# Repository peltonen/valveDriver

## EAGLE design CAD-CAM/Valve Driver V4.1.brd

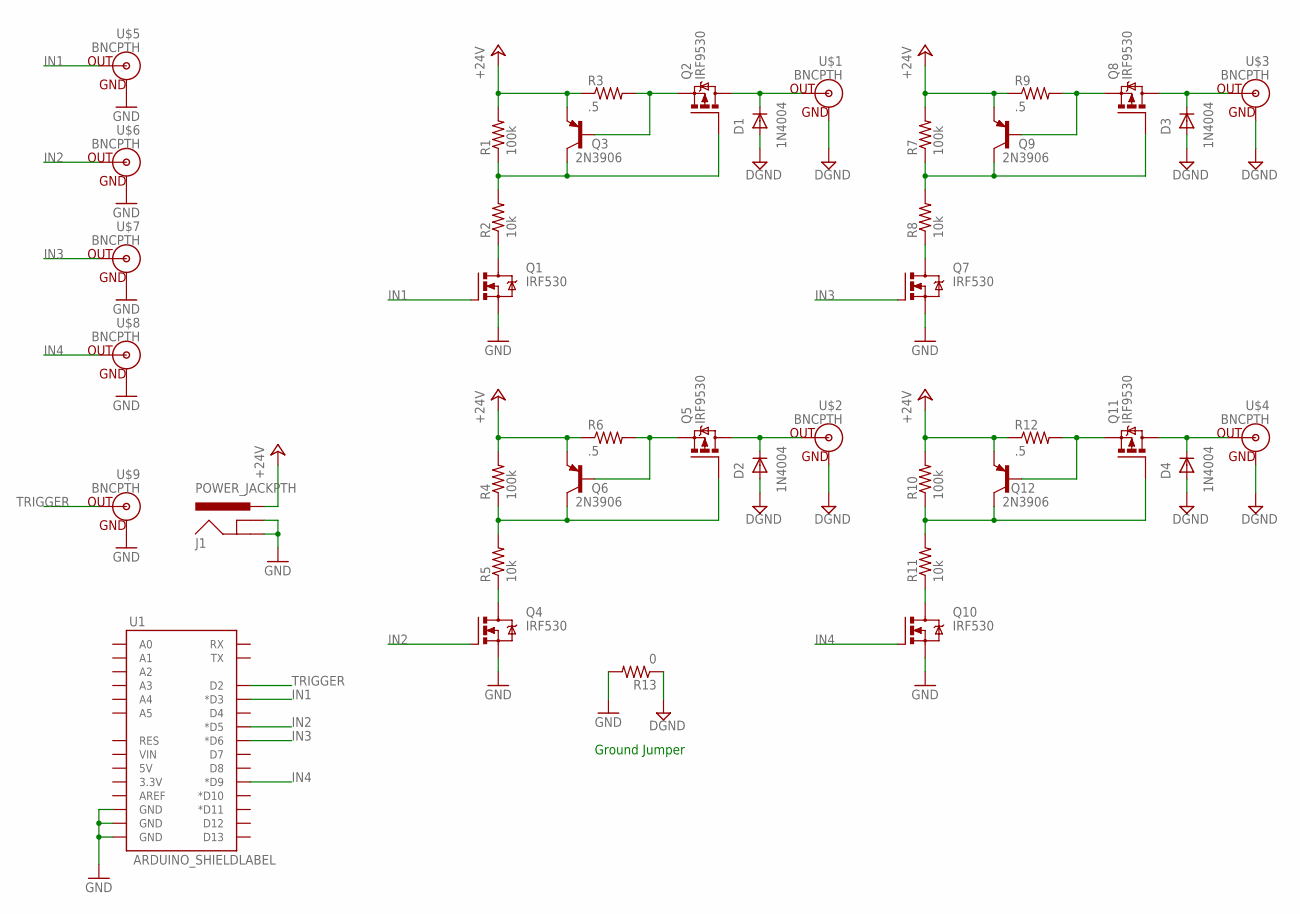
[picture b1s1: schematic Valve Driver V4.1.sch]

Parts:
D1, D2, D3, D4: 1N4004; DO41-10
J1: POWER_JACKPTH; POWER_JACK_PTH
Q1, Q4, Q7, Q10: IRF530; TO220BV
Q2, Q5, Q8, Q11: IRF9530; TO220BV
Q3, Q6, Q9, Q12: 2N3906; TO92
R1, R4, R7, R10: 100k; AXIAL-0.4
R2, R5, R8, R11: 10k; AXIAL-0.4
R3, R6, R9, R12: .5; AXIAL-0.4
R13: 0; AXIAL-0.4
U1: ARDUINO_SHIELDLABEL; DUEMILANOVE_SHIELD
U$1, U$2, U$3, U$4, U$5, U$6, U$7, U$8, U$9: BNCPTH; BNC

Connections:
+24V: J1.PWR, Q3.3 (E), Q6.3 (E), Q9.3 (E), Q12.3 (E), R1.P$2 (2), R3.P$1 (1), R4.P$2 (2), R6.P$1 (1), R7.P$2 (2), R9.P$1 (1), R10.P$2 (2), R12.P$1 (1)
DGND: D1.A, D2.A, D3.A, D4.A, R13.P$1 (1), U$1.GND, U$2.GND, U$3.GND, U$4.GND
GND: J1.GND, J1.GNDBREAK, Q1.S, Q4.S, Q7.S, Q10.S, R13.P$2 (2), U1.GND@0 (GND), U1.GND@1 (GND), U1.GND@2 (GND), U$5.GND, U$6.GND, U$7.GND, U$8.GND, U$9.GND
IN1: Q1.G, U1.D3 (*D3), U$5.S (OUT)
IN2: Q4.G, U1.D5 (*D5), U$6.S (OUT)
IN3: Q7.G, U1.D6 (*D6), U$7.S (OUT)
IN4: Q10.G, U1.D9 (*D9), U$8.S (OUT)
unnamed: Q2.G, Q3.1 (C), R1.P$1 (1), R2.P$2 (2)
unnamed: Q1.D, R2.P$1 (1)
unnamed: Q2.S, Q3.2 (B), R3.P$2 (2)
unnamed: D1.C, Q2.D, U$1.S (OUT)
unnamed: Q5.G, Q6.1 (C), R4.P$1 (1), R5.P$2 (2)
unnamed: Q4.D, R5.P$1 (1)
unnamed: Q5.S, Q6.2 (B), R6.P$2 (2)
unnamed: D2.C, Q5.D, U$2.S (OUT)
unnamed: Q8.G, Q9.1 (C), R7.P$1 (1), R8.P$2 (2)
unnamed: Q7.D, R8.P$1 (1)
unnamed: Q8.S, Q9.2 (B), R9.P$2 (2)
unnamed: D3.C, Q8.D, U$3.S (OUT)
unnamed: Q11.G, Q12.1 (C), R10.P$1 (1), R11.P$2 (2)
unnamed: Q10.D, R11.P$1 (1)
unnamed: Q11.S, Q12.2 (B), R12.P$2 (2)
unnamed: D4.C, Q11.D, U$4.S (OUT)
TRIGGER: U1.D2, U$9.S (OUT)

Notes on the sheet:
Ground Jumper

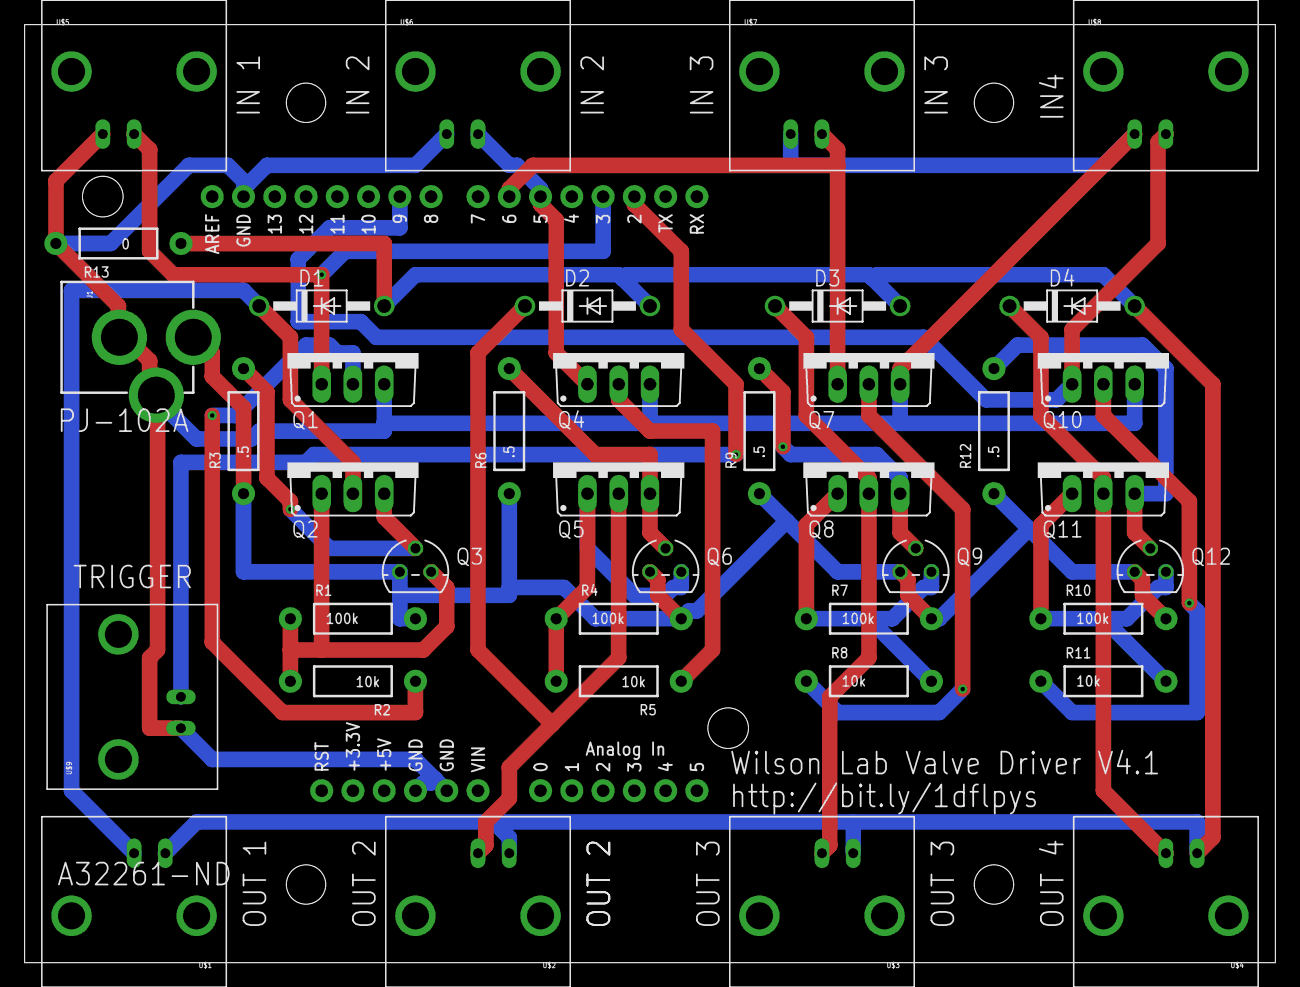
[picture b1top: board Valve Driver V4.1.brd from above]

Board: 2 copper layers, 101.6 x 76.2 mm, 40 parts (0 on the bottom side), 24 nets.

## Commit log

2014-03-22 Moved files around
2014-04-25 Updated BOM to correct power supply. Old supply was pin-negative. Correct is pin-positive
2014-12-25 added Arduino control sketch

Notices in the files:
parts and their libraries:
SparkFun-Connectors: Licensing: CC v3.0 Share-Alike You are welcome to use this library for commercial purposes.
